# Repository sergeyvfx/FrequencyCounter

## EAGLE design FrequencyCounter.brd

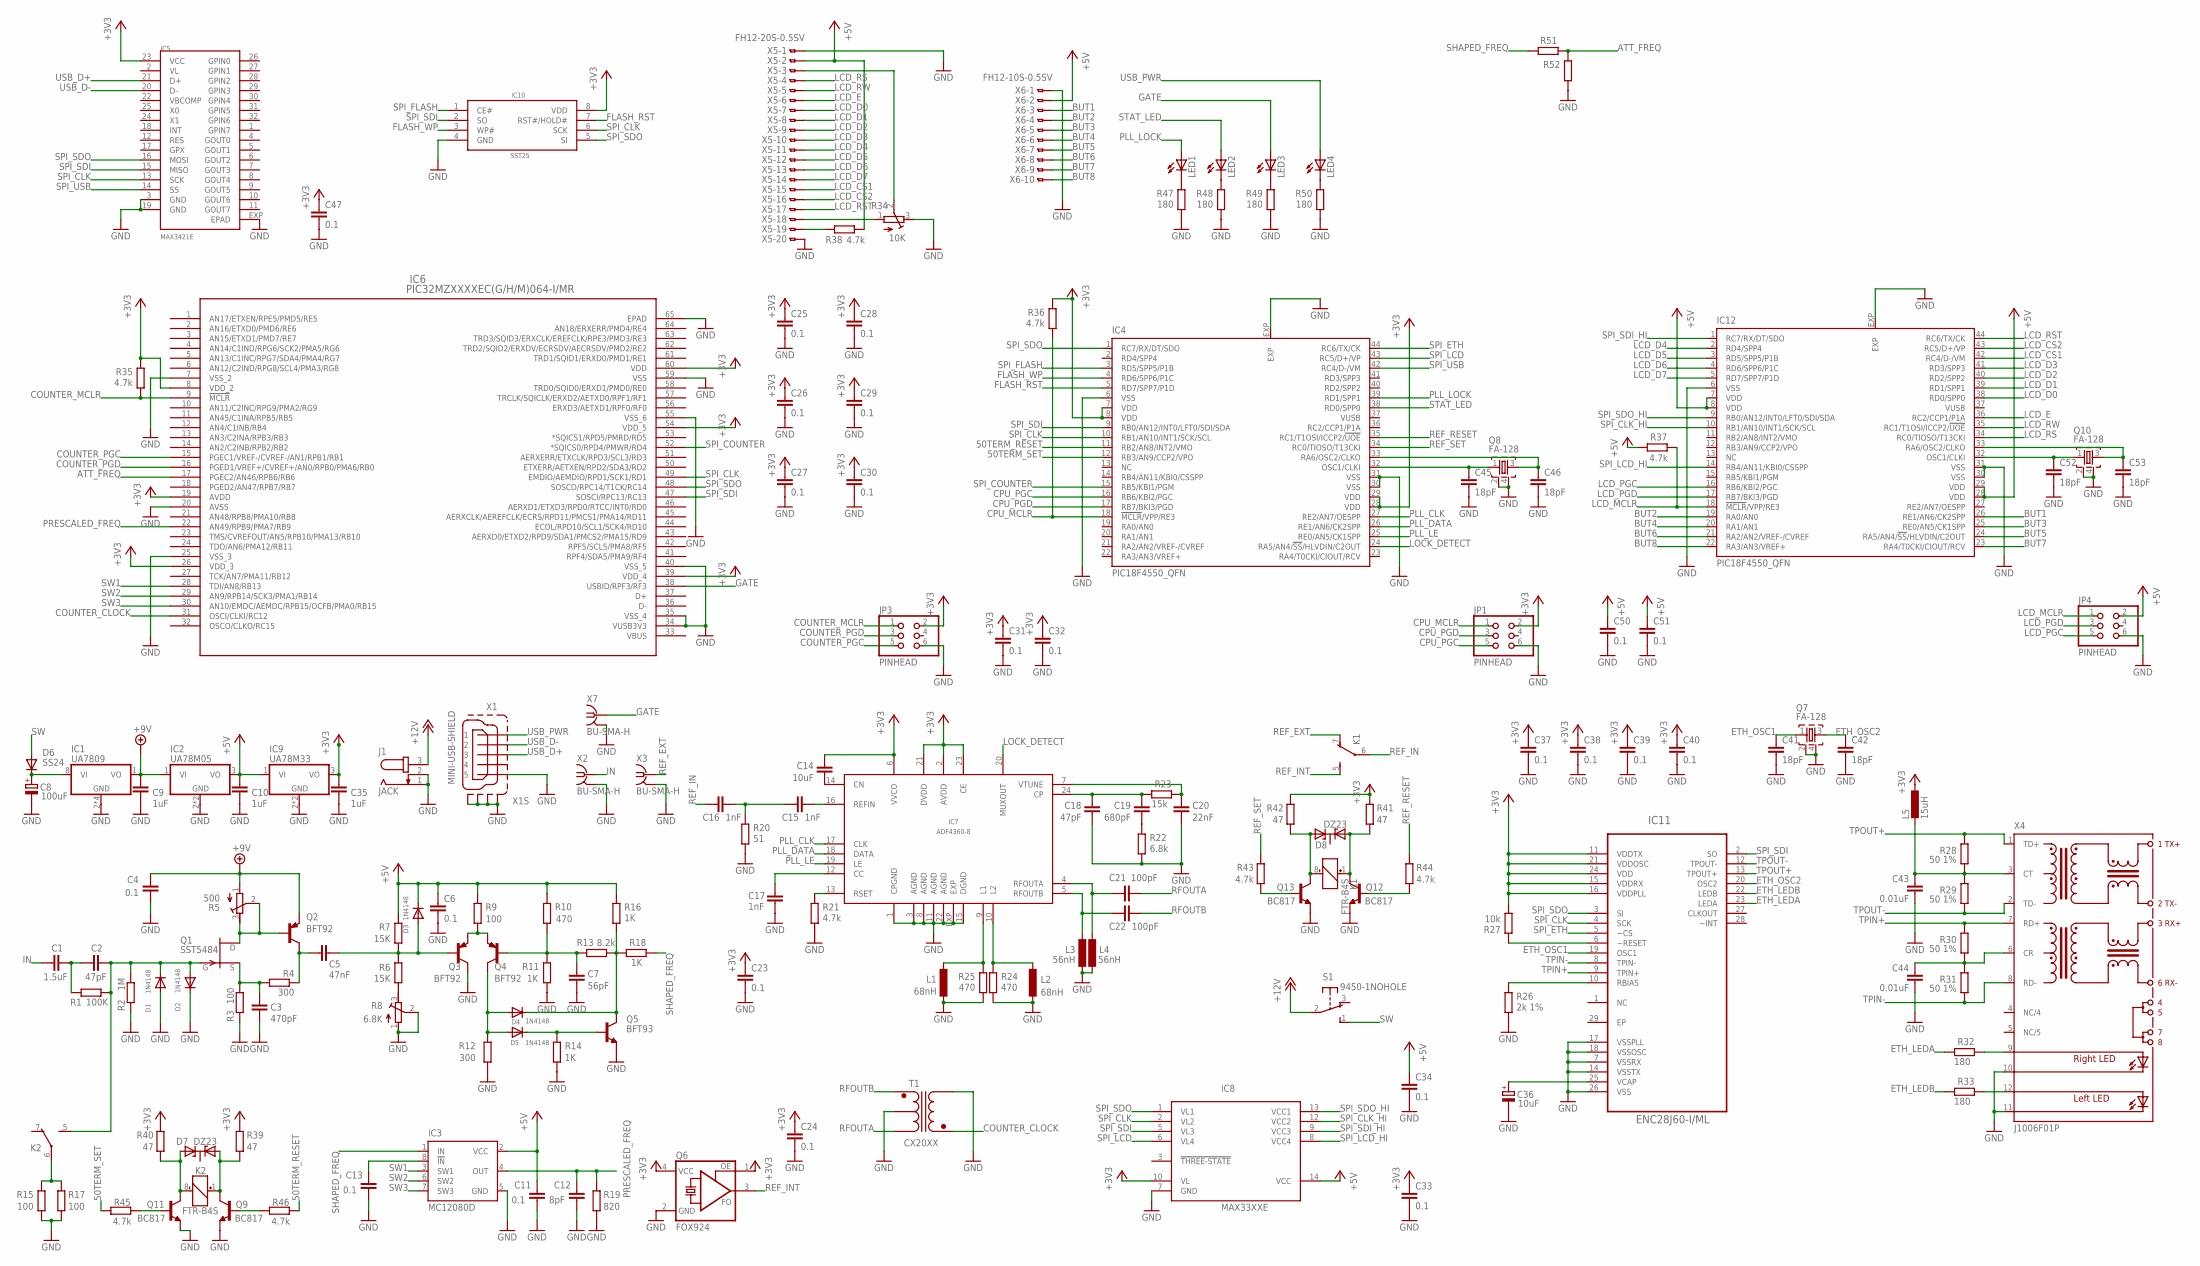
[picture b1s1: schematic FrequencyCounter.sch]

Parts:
C1: 1.5uF; C0603
C2, C18: 47pF; C0603
C3: 470pF; C0603
C4, C6, C11, C13, C23, C24, C25, C26, C27, C28, C29, C30, C31, C32, C33, C34, C37, C38, C39, C40, C47, C50, C51: 0.1; C0603
C5: 47nF; C0603
C7: 56pF; C0603
C8: 100uF; D/7343-31R
C9, C10, C35: 1uF; C0603
C12: 8pF; C0603
C14: 10uF; C0603
C15, C16, C17: 1nF; C0603
C19: 680pF; C0603
C20: 22nF; C0603
C21, C22: 100pF; C0603
C36: 10uF; B/3528-21R
C41, C42, C45, C46, C52, C53: 18pF; C0603
C43, C44: 0.01uF; C0603
D1, D2, D3, D4, D5: 1N4148; SOD-123
D6: SS24; DO214AA
D7, D8: DZ23; SOT23
IC1: UA7809; SOIC8
IC2: UA78M05; SOT223
IC3: MC12080D; SO08
IC4, IC12: PIC18F4550_QFN; QFN44ML8X8
IC5: MAX3421E; TQFN32
IC6: PIC32MZXXXXEC(G/H/M)064-I/MR; QFN64_9X9MC
IC7: ADF4360-8; LFCSP24
IC8: MAX33XXE; TSSOP14
IC9: UA78M33; SOT223
IC10: SST25; SOIC8
IC11: ENC28J60-I/ML; QFN65P600X600X100-29N
J1: JACK; SPC4077
JP1, JP3, JP4: PINHEAD; 2X03_1.27
K1, K2: FTR-B4S
L1, L2: 68nH; L2012C
L3, L4: 56nH; L2012C
L5: 15uH; L2012C
LED1, LED2, LED3, LED4: LEDCHIP-LED0805; CHIP-LED0805
Q1: SST5484; SOT23
Q2, Q3, Q4: BFT92; SOT23-BEC
Q5: BFT93; SOT23-BEC
Q6: FOX924
Q7, Q8, Q10: FA-128
Q9, Q11, Q12, Q13: BC817; SOT23-BEC
R1: 100K; R0603
R2: 1M; R0603
R3, R9, R15, R17: 100; R0603
R4, R12: 300; R0603
R5: 500; RTRIM4G/J
R6, R7: 15K; R0603
R8: 6.8K; RTRIM4G/J
R10, R24, R25: 470; R0603
R11, R14, R16, R18: 1K; R0603
R13: 8.2k; R0603
R19: 820; R0603
R20: 51; R0603
R21, R35, R36, R37, R38, R43, R44, R45, R46: 4.7k; R0603
R22: 6.8k; R0603
R23: 15k; R0603
R26: 2k 1%; R0603
R27: 10k; R0603
R28, R29, R30, R31: 50 1%; R0603
R32, R33, R47, R48, R49, R50: 180; R0603
R34: 10K; RTRIM4G/J
R39, R40, R41, R42: 47; R0603
R51, R52: R-EU_R0603; R0603
S1: 9450-1NOHOLE; 9450-1-NOHOLE
T1: CX20XX; PULSE_CX20
X1: MINI-USB-SHIELD; UX60A-MB-5ST
X2, X3, X7: BU-SMA-H
X4: J1006F01P; J1
X5: FH12-20S-0.5SV
X6: FH12-10S-0.5SV

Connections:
50TERM_RESET: IC4.11 (RB2/AN8/INT2/VMO), R46.2
50TERM_SET: IC4.12 (RB3/AN9/CCP2/VPO), R45.1
+3V3: C14.2, C23.1, C24.1, C25.1, C26.1, C27.1, C28.1, C29.1, C30.1, C31.1, C32.1, C33.1, C35.1, C37.1, C38.1, C39.1, C40.1, C47.1, IC4.7 (VDD), IC4.8 (VDD), IC4.28 (VDD), IC4.29 (VDD), IC5.23 (VCC), IC6.8 (VDD_2), IC6.19 (AVDD), IC6.26 (VDD_3), IC6.39 (VDD_4), IC6.54 (VDD_5), IC6.60 (VDD), IC7.2 (AVDD), IC7.6 (VVCO), IC7.21 (DVDD), IC7.23 (CE), IC8.10 (VL), IC9.3 (VO), IC10.8 (VDD), IC11.11 (VDDTX), IC11.15 (VDDRX), IC11.16 (VDDPLL), IC11.21 (VDDOSC), IC11.24 (VDD), JP1.2, JP3.2, L5.1, Q6.1 (OE), Q6.4 (VCC), R27.2, R35.1, R36.1, R39.1, R40.1, R41.1, R42.1
+5V: C6.1, C10.1, C11.1, C34.1, C50.1, C51.1, D3.C, IC2.3 (VO), IC3.2 (VCC), IC8.14 (VCC), IC9.1 (VI), IC12.7 (VDD), IC12.8 (VDD), IC12.28 (VDD), IC12.29 (VDD), JP4.2, R7.1, R9.1, R10.1, R16.1, R37.1, R38.2, X5.2, X6.2
+9V: C4.1, C9.1, IC1.1 (VO), IC2.1 (VI), Q2.E, R5.1 (A)
+12V: J1.3, S1.2
ATT_FREQ: IC6.17 (PGEC2/AN46/RPB6/RB6), R51.2, R52.1
BUT1: IC12.26 (RE1/AN6/CK2SPP), X6.3
BUT2: IC12.19 (RA0/AN0), X6.4
BUT3: IC12.25 (RE0/AN5/CK1SPP), X6.5
BUT4: IC12.20 (RA1/AN1), X6.6
BUT5: IC12.24 (RA5/AN4/!SS!/HLVDIN/C2OUT), X6.7
BUT6: IC12.21 (RA2/AN2/VREF-/CVREF), X6.8
BUT7: IC12.23 (RA4/T0CKI/CIOUT/RCV), X6.9
BUT8: IC12.22 (RA3/AN3/VREF+), X6.10
COUNTER_CLOCK: IC6.31 (OSCI/CLKI/RC12), T1.P$4
COUNTER_MCLR: IC6.9 (!MCLR!), JP3.1, R35.2
COUNTER_PGC: IC6.15 (PGEC1/VREF-/CVREF-/AN1/RPB1/RB1), JP3.5
COUNTER_PGD: IC6.16 (PGED1/VREF+/CVREF+/AN0/RPB0/PMA6/RB0), JP3.3
CPU_MCLR: IC4.18 (!MCLR!/VPP/RE3), JP1.1, R36.2
CPU_PGC: IC4.16 (RB6/KBI2/PGC), JP1.5
CPU_PGD: IC4.17 (RB7/BKI3/PGD), JP1.3
ETH_LEDA: IC11.23 (LEDA), R32.2
ETH_LEDB: IC11.22 (LEDB), R33.2
ETH_OSC1: C41.1, IC11.19 (OSC1), Q7.1
ETH_OSC2: C42.1, IC11.20 (OSC2), Q7.3
FLASH_RST: IC4.5 (RD7/SPP7/P1D), IC10.7 (RST#/HOLD#)
FLASH_WP: IC4.4 (RD6/SPP6/P1C), IC10.3 (WP#)
GATE: IC6.38 (USBID/RPF3/RF3), LED3.A, X7.1
GND: C3.2, C4.2, C6.2, C7.1, C8.-, C9.2, C10.2, C11.2, C12.2, C13.2, C17.2, C18.1, C20.1, C23.2, C24.2, C25.2, C26.2, C27.2, C28.2, C29.2, C30.2, C31.2, C32.2, C33.2, C34.2, C35.2, C36.-, C37.2, C38.2, C39.2, C40.2, C41.2, C42.2, C43.2, C44.2, C45.2, C46.2, C47.2, C50.2, C51.2, C52.2, C53.2, D1.A, D2.C, IC1.2 (GND), IC1.3 (GND), IC1.6 (GND), IC1.7 (GND), IC2.2 (GND), IC2.4 (GND), IC3.5 (GND), IC4.6 (VSS), IC4.30 (VSS), IC4.31 (VSS), IC4.EXP, IC5.3 (GND), IC5.19 (GND), IC5.EXP (EPAD), IC6.7 (VSS_2), IC6.20 (AVSS), IC6.25 (VSS_3), IC6.34 (VUSB3V3), IC6.35 (VSS_4), IC6.40 (VSS_5), IC6.55 (VSS_6), IC6.59 (VSS), IC6.65 (EPAD), IC7.1 (CPGND), IC7.3 (AGND), IC7.8 (AGND), IC7.11 (AGND), IC7.15 (DGND), IC7.22 (AGND), IC7.EXP, IC8.7 (GND), IC9.2 (GND), IC9.4 (GND), IC10.4 (GND), IC11.7 (VSSRX), IC11.14 (VSSTX), IC11.17 (VSSPLL), IC11.18 (VSSOSC), IC11.26 (VSS), IC12.6 (VSS), IC12.30 (VSS), IC12.31 (VSS), IC12.EXP, J1.1, J1.2, JP1.6, JP3.6, JP4.6, L1.2, L2.2, L3.2, L4.2, Q3.C, Q5.E, Q6.2 (GND), Q7.2, Q7.4, Q8.2, Q8.4, Q9.E, Q10.2, Q10.4, Q11.E, Q12.E, Q13.E, R2.2, R3.2, R8.1 (A), R8.2 (S), R11.2, R12.2, R14.2, R15.2, R17.2, R19.2, R20.2, R21.2, R22.2, R24.2, R25.2, R26.2, R34.3 (E), R47.2, R48.2, R49.2, R50.2, R52.2, T1.P$2, T1.P$6, X1.5, X1.M1 (S1), X1.M2 (S2), X1.M3 (S3), X1.M4 (S4), X2.2, X2.3 (2), X2.4 (2), X2.5 (2), X3.2, X3.3 (2), X3.4 (2), X3.5 (2), X4.10 (C-R), X4.11 (C-L), X5.1, X5.20, X6.1, X7.2, X7.3 (2), X7.4 (2), X7.5 (2)
IN: C1.1, X2.1
LCD_CS1: IC12.42 (RC4/D-/VM), X5.15
LCD_CS2: IC12.43 (RC5/D+/VP), X5.16
LCD_D0: IC12.38 (RD0/SPP0), X5.7
LCD_D1: IC12.39 (RD1/SPP1), X5.8
LCD_D2: IC12.40 (RD2/SPP2), X5.9
LCD_D3: IC12.41 (RD3/SPP3), X5.10
LCD_D4: IC12.2 (RD4/SPP4), X5.11
LCD_D5: IC12.3 (RD5/SPP5/P1B), X5.12
LCD_D6: IC12.4 (RD6/SPP6/P1C), X5.13
LCD_D7: IC12.5 (RD7/SPP7/P1D), X5.14
LCD_E: IC12.36 (RC2/CCP1/P1A), X5.6
LCD_MCLR: IC12.18 (!MCLR!/VPP/RE3), JP4.1, R37.2
LCD_PGC: IC12.16 (RB6/KBI2/PGC), JP4.5
LCD_PGD: IC12.17 (RB7/BKI3/PGD), JP4.3
LCD_RS: IC12.34 (RC0/TIOSO/T13CKI), X5.4
LCD_RST: IC12.44 (RC6/TX/CK), X5.17
LCD_RW: IC12.35 (RC1/T1OSI/ICCP2/!UOE), X5.5
LOCK_DETECT: IC4.24 (RA5/AN4/!SS!/HLVDIN/C2OUT), IC7.20 (MUXOUT)
unnamed: C2.2, D1.C, D2.A, K2.5 (S), Q1.3 (G), R1.1, R2.1
unnamed: C1.2, C2.1, R1.2
unnamed: C3.1, Q1.2 (S), R3.1, R4.2
unnamed: Q1.1 (D), Q2.B, R5.2 (S), R5.3 (E)
unnamed: C5.2, Q2.C, R4.1
unnamed: R6.2, R8.3 (E)
unnamed: C5.1, D3.A, Q3.B, R6.1, R7.2
unnamed: Q3.E, Q4.E, R9.2
unnamed: C7.2, Q4.B, R10.2, R11.1, R13.2
unnamed: D4.A, D5.A, Q4.C, R12.1
unnamed: D4.C, Q5.C, R13.1, R16.2, R18.2
unnamed: D5.C, Q5.B, R14.1
unnamed: C8.+, D6.C, IC1.8 (VI)
unnamed: K2.6, R15.1, R17.1
unnamed: C14.1, IC7.14 (CN)
unnamed: C13.1, IC3.8 (!IN)
unnamed: C15.1, IC7.16 (REFIN)
unnamed: C15.2, C16.1, R20.1
unnamed: C17.1, IC7.12 (CC)
unnamed: IC7.13 (RSET), R21.1
unnamed: C19.1, R22.1
unnamed: C21.1, IC7.4 (RFOUTA), L4.1
unnamed: C20.2, IC7.7 (VTUNE), R23.1
unnamed: C18.2, C19.2, IC7.24 (CP), R23.2
unnamed: C22.2, IC7.5 (RFOUTB), L3.1
unnamed: IC7.10 (L2), L2.1, R24.1
unnamed: IC7.9 (L1), L1.1, R25.1
unnamed: C53.1, IC12.33 (RA6/OSC2/CLKO), Q10.3
unnamed: C46.1, IC4.33 (RA6/OSC2/CLKO), Q8.3
unnamed: C45.1, IC4.32 (OSC1/CLKI), Q8.1
unnamed: C36.+, IC11.25 (VCAP)
unnamed: IC11.10 (RBIAS), R26.1
unnamed: C43.1, L5.2, R28.1, R29.2, X4.3 (CT)
unnamed: IC11.6 (~RESET), R27.1
unnamed: R32.1, X4.9 (A-R)
unnamed: R33.1, X4.12 (A-L)
unnamed: C44.1, R30.1, R31.2, X4.6 (CR)
unnamed: C52.1, IC12.32 (OSC1/CLKI), Q10.1
unnamed: R34.2 (S), X5.3
unnamed: R34.1 (A), X5.18
unnamed: R38.1, X5.19
unnamed: D7.2 (A2), K2.8 (-), Q11.C, R40.2
unnamed: D8.2 (A2), K1.8 (-), Q13.C, R42.2
unnamed: D7.1 (A1), K2.1 (+), Q9.C, R39.2
unnamed: D8.1 (A1), K1.1 (+), Q12.C, R41.2
unnamed: Q13.B, R43.2
unnamed: Q12.B, R44.2
unnamed: Q11.B, R45.2
unnamed: Q9.B, R46.1
unnamed: LED1.C, R47.1
unnamed: LED2.C, R48.1
unnamed: LED3.C, R49.1
unnamed: LED4.C, R50.1
PLL_CLK: IC4.27 (RE2/AN7/OESPP), IC7.17 (CLK)
PLL_DATA: IC4.26 (RE1/AN6/CK2SPP), IC7.18 (DATA)
PLL_LE: IC4.25 (RE0/AN5/CK1SPP), IC7.19 (LE)
PLL_LOCK: IC4.39 (RD1/SPP1), LED1.A
PRESCALED_FREQ: C12.1, IC3.4 (OUT), IC6.22 (AN49/RPB9/PMA7/RB9), R19.1
REF_EXT: K1.7 (O), X3.1
REF_IN: C16.2, K1.6
REF_INT: K1.5 (S), Q6.3 (FO)
REF_RESET: IC4.35 (RC1/T1OSI/ICCP2/!UOE), R44.1
REF_SET: IC4.34 (RC0/TIOSO/T13CKI), R43.1
RFOUTA: C21.2, T1.P$3
RFOUTB: C22.1, T1.P$1
SHAPED_FREQ: IC3.1 (IN), R18.1, R51.1
SPI_CLK: IC4.10 (RB1/AN10/INT1/SCK/SCL), IC5.13 (SCK), IC6.49 (EMDIO/AEMDIO/RPD1/SCK1/RD1), IC8.2 (VL2), IC10.6 (SCK), IC11.4 (SCK)
SPI_CLK_HI: IC8.12 (VCC2), IC12.10 (RB1/AN10/INT1/SCK/SCL)
SPI_COUNTER: IC4.15 (RB5/KBI1/PGM), IC6.52 (*SQICS0/RPD4/PMWR/RD4)
SPI_ETH: IC4.44 (RC6/TX/CK), IC11.5 (~CS)
SPI_FLASH: IC4.3 (RD5/SPP5/P1B), IC10.1 (CE#)
SPI_LCD: IC4.43 (RC5/D+/VP), IC8.6 (VL4)
SPI_LCD_HI: IC8.8 (VCC4), IC12.14 (RB4/AN11/KBI0/CSSPP)
SPI_SDI: IC4.9 (RB0/AN12/INT0/LFT0/SDI/SDA), IC5.15 (MISO), IC6.47 (SOSCI/RPC13/RC13), IC8.5 (VL3), IC10.2 (SO), IC11.2 (SO)
SPI_SDI_HI: IC8.9 (VCC3), IC12.1 (RC7/RX/DT/SDO)
SPI_SDO: IC4.1 (RC7/RX/DT/SDO), IC5.16 (MOSI), IC6.48 (SOSCO/RPC14/T1CK/RC14), IC8.1 (VL1), IC10.5 (SI), IC11.3 (SI)
SPI_SDO_HI: IC8.13 (VCC1), IC12.9 (RB0/AN12/INT0/LFT0/SDI/SDA)
SPI_USB: IC4.42 (RC4/D-/VM), IC5.14 (SS)
STAT_LED: IC4.38 (RD0/SPP0), LED2.A
SW: D6.A, S1.1 (S)
SW1: IC3.3 (SW1), IC6.28 (TDI/AN8/RB13)
SW2: IC3.6 (SW2), IC6.29 (AN9/RPB14/SCK3/PMA1/RB14)
SW3: IC3.7 (SW3), IC6.30 (AN10/EMDC/AEMDC/RPB15/OCFB/PMA0/RB15)
TPIN+: IC11.9 (TPIN+), R30.2, X4.7 (RD+)
TPIN-: IC11.8 (TPIN-), R31.1, X4.8 (RD-)
TPOUT+: IC11.13 (TPOUT+), R28.2, X4.1 (TD+)
TPOUT-: IC11.12 (TPOUT-), R29.1, X4.2 (TD-)
USB_D+: IC5.21 (D+), X1.3
USB_D-: IC5.20 (D-), X1.2
USB_PWR: LED4.A, X1.1
VBUS: IC6.33 (VBUS)

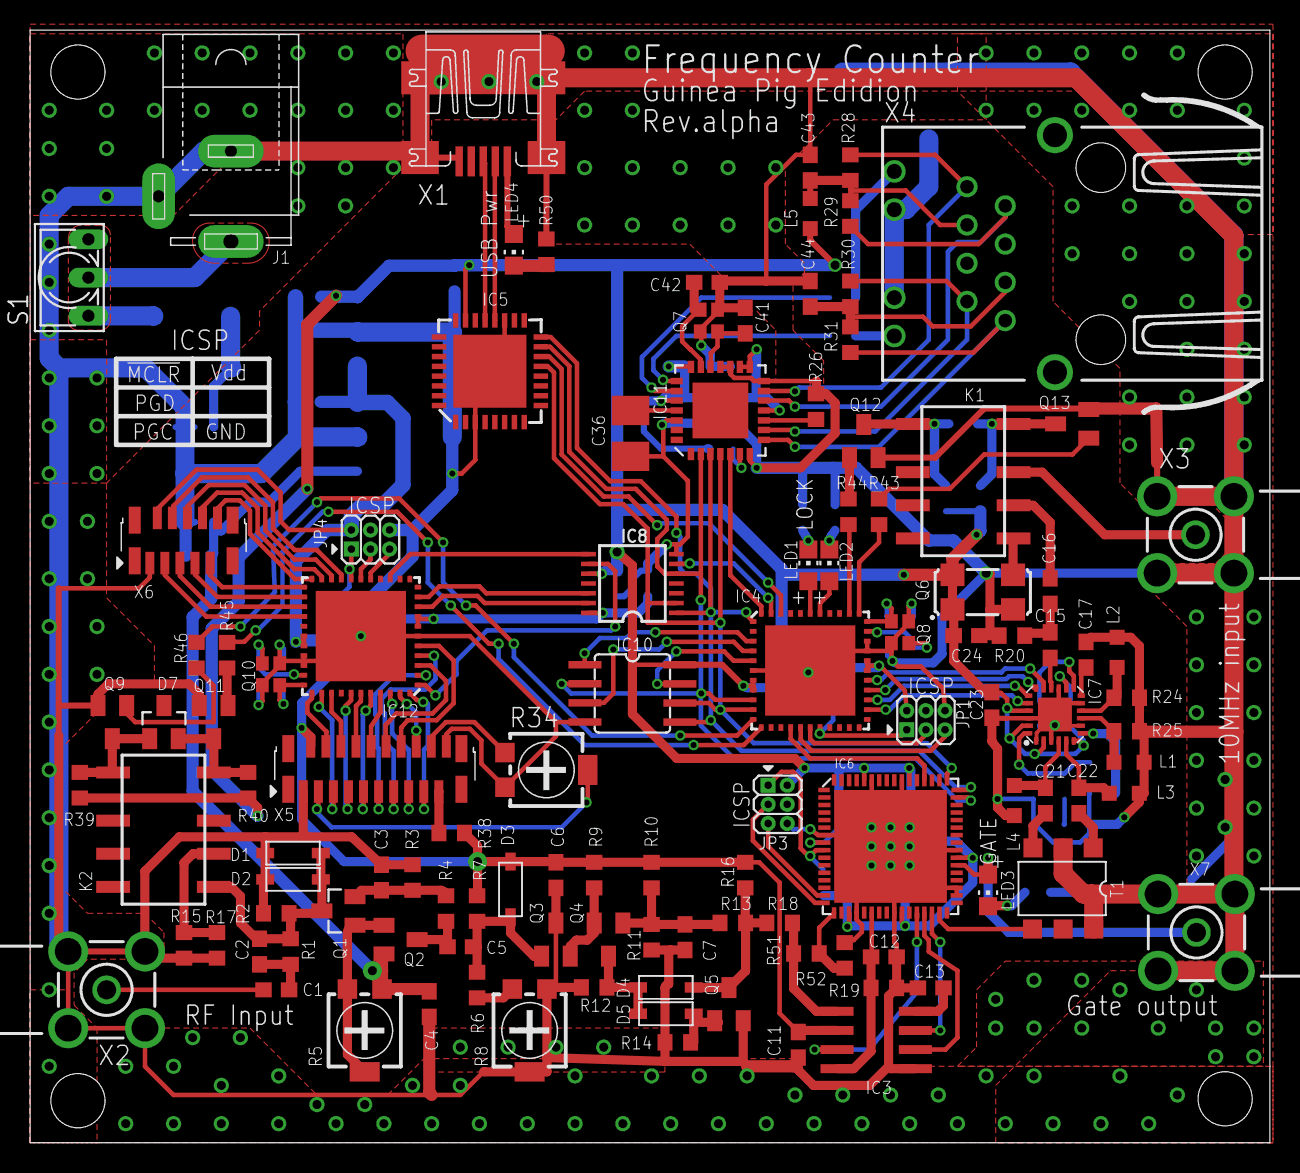
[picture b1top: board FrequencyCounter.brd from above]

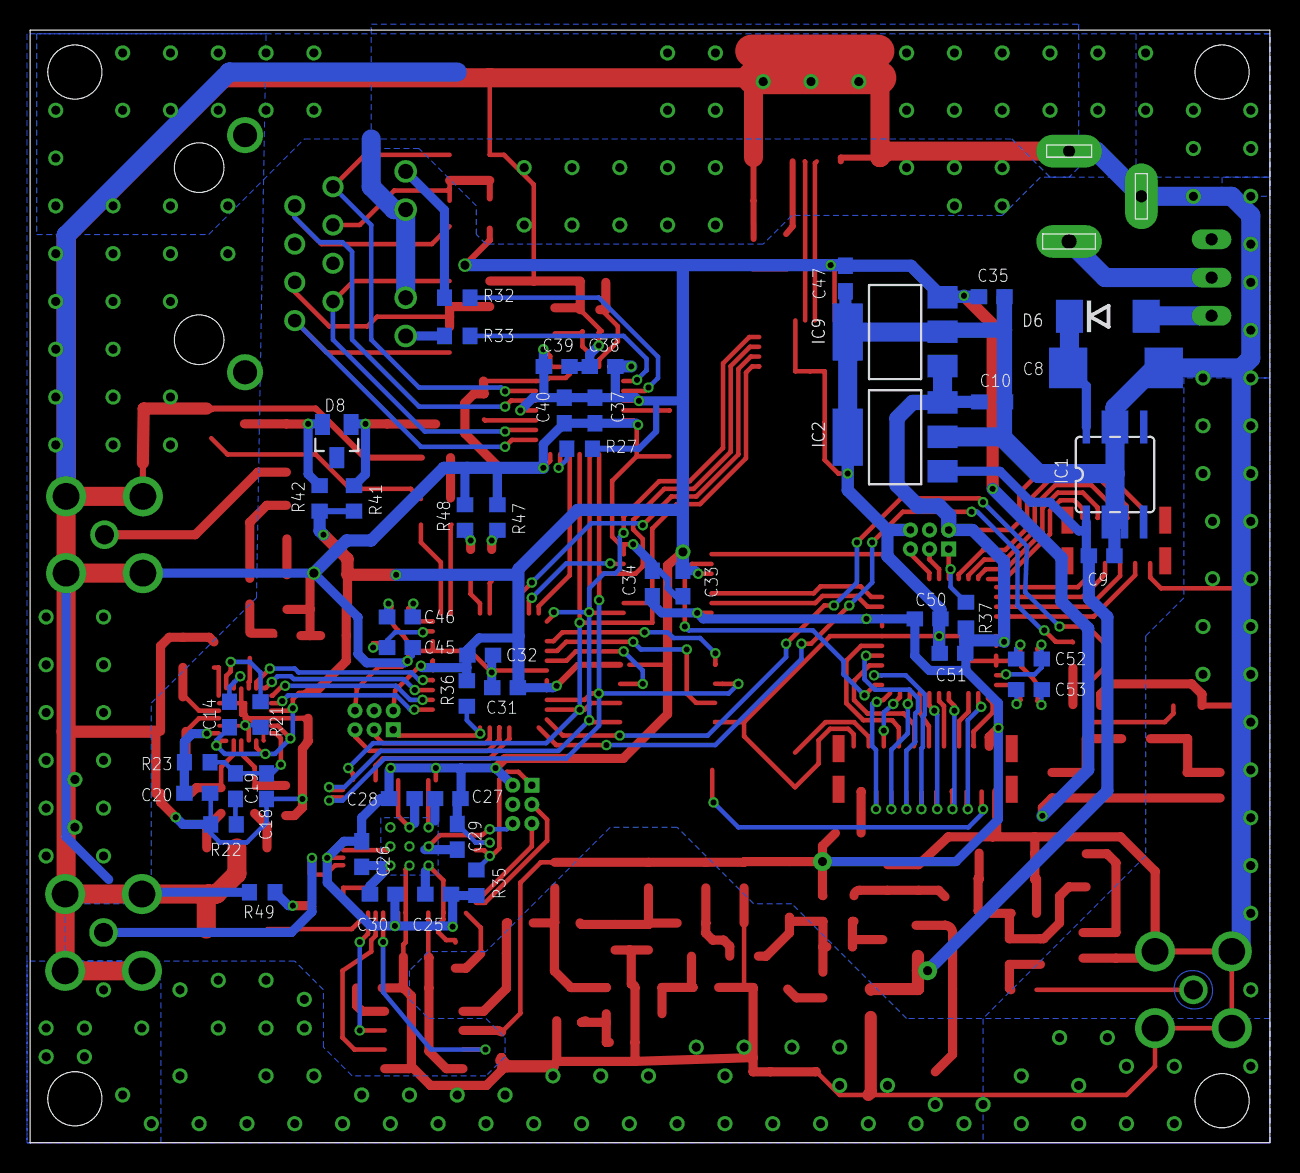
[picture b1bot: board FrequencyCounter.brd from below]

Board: 2 copper layers, 82.3 x 73.9 mm, 160 parts (48 on the bottom side), 139 nets.

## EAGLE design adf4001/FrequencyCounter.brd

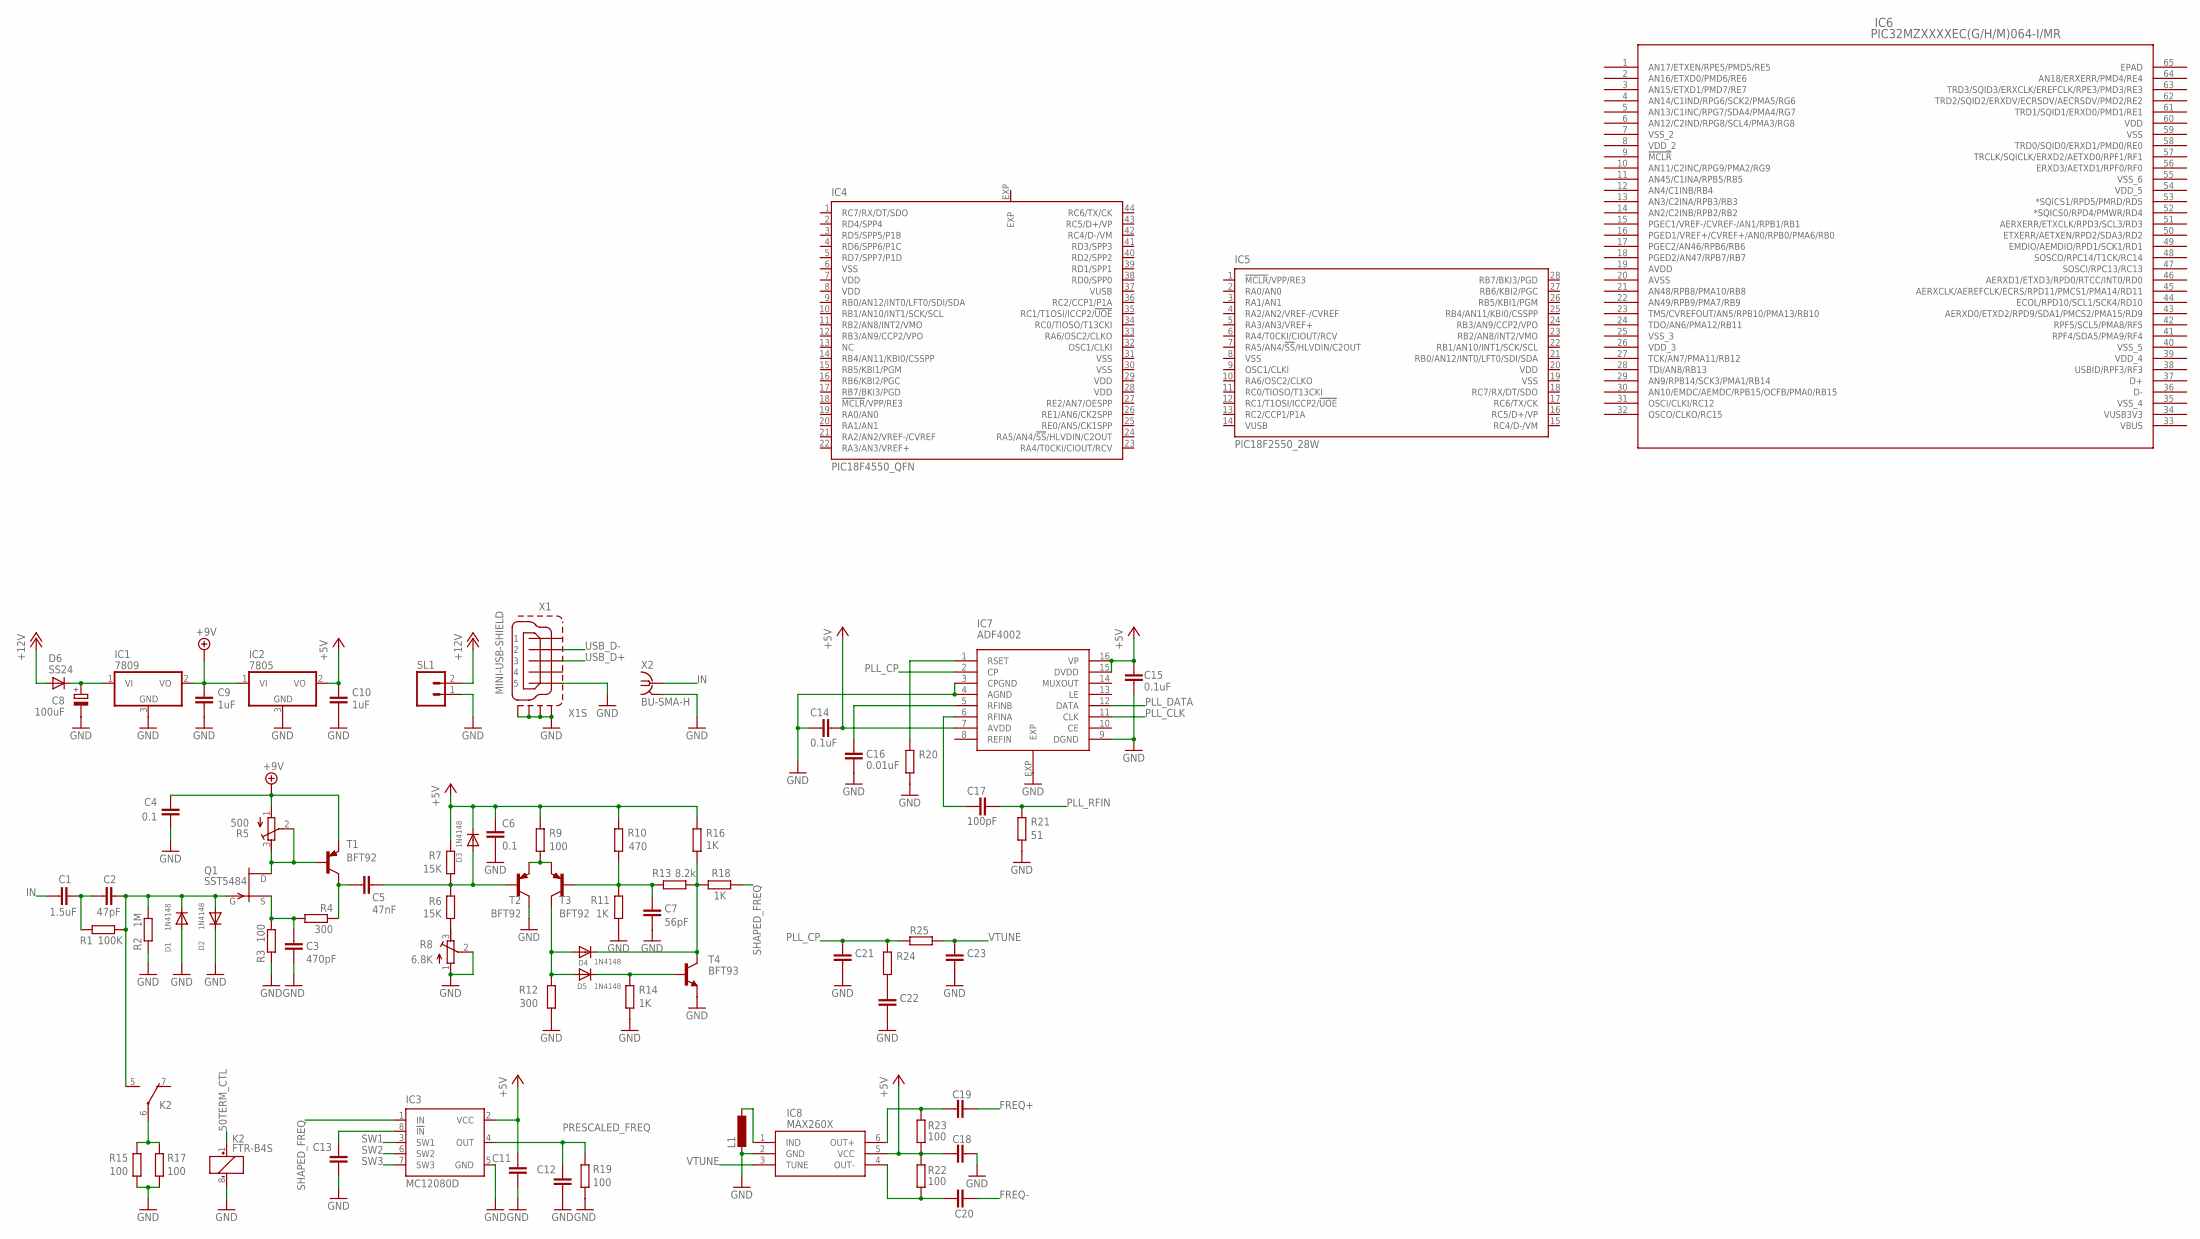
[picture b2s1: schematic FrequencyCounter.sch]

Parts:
C1: 1.5uF; C0805
C2: 47pF; C0805
C3: 470pF; C0805
C4, C6: 0.1; C0805
C5: 47nF; C0805
C7: 56pF; C0805
C8: 100uF; D/7343-31R
C9, C10: 1uF; C0805
C11, C12, C13, C18, C19, C20, C21, C22, C23: C-EUC0805; C0805
C14, C15: 0.1uF; C0805
C16: 0.01uF; C0805
C17: 100pF; C0805
D1, D2, D3, D4, D5: 1N4148; SOD-123
D6: SS24; DO214AA
IC1: 7809; TO252
IC2: 7805; TO252
IC3: MC12080D; SO08
IC4: PIC18F4550_QFN; QFN44ML8X8
IC5: PIC18F2550_28W; SO28W
IC6: PIC32MZXXXXEC(G/H/M)064-I/MR; QFN64_9X9MC
IC7: ADF4002; LFCSP16
IC8: MAX260X; SOT-23-6
K2: FTR-B4S
L1: L-EUL3225P; L3225P
Q1: SST5484; SOT23
R1: 100K; R0805
R2: 1M; R0805
R3, R9, R15, R17, R19, R22, R23: 100; R0805
R4, R12: 300; R0805
R5: 500; RTRIM4G/J
R6, R7: 15K; R0805
R8: 6.8K; RTRIM4G/J
R10: 470; R0805
R11, R14, R16, R18: 1K; R0805
R13: 8.2k; R0805
R20, R24, R25: R-EU_R0805; R0805
R21: 51; R0805
SL1: M02; 02P
T1, T2, T3: BFT92; SOT23-BEC
T4: BFT93; SOT23-BEC
X1: MINI-USB-SHIELD; UX60A-MB-5ST
X2: BU-SMA-H

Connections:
50TERM_CTL: K2.1 (+)
+5V: C6.1, C10.1, C11.1, C14.1, C15.2, C18.1, D3.C, IC2.2 (VO), IC3.2 (VCC), IC7.7 (AVDD), IC7.15 (DVDD), IC7.16 (VP), IC8.5 (VCC), R7.1, R9.1, R10.1, R16.1, R22.2, R23.1
+9V: C4.1, C9.1, IC1.2 (VO), IC2.1 (VI), R5.1 (A), T1.E
+12V: D6.A, SL1.2
AVDD: IC6.19 (AVDD)
AVSS: IC6.20 (AVSS)
FREQ+: C19.2
FREQ-: C20.2
GND: C3.2, C4.2, C6.2, C7.1, C8.-, C9.2, C10.2, C11.2, C12.2, C13.2, C14.2, C15.1, C16.2, C18.2, C21.1, C22.1, C23.1, D1.A, D2.C, IC1.3 (GND), IC2.3 (GND), IC3.5 (GND), IC7.3 (CPGND), IC7.4 (AGND), IC7.9 (DGND), IC7.EXP, IC8.2 (GND), K2.8 (-), L1.2, R2.2, R3.2, R8.1 (A), R8.2 (S), R11.2, R12.2, R14.2, R15.2, R17.2, R19.2, R20.2, R21.2, SL1.1, T2.C, T4.E, X1.5, X1.M1 (S1), X1.M2 (S2), X1.M3 (S3), X1.M4 (S4), X2.2, X2.3 (2), X2.4 (2), X2.5 (2)
IN: C1.1, X2.1
unnamed: C2.2, D1.C, D2.A, K2.5 (S), Q1.3 (G), R1.1, R2.1
unnamed: C1.2, C2.1, R1.2
unnamed: C3.1, Q1.2 (S), R3.1, R4.2
unnamed: Q1.1 (D), R5.2 (S), R5.3 (E), T1.B
unnamed: C5.2, R4.1, T1.C
unnamed: R6.2, R8.3 (E)
unnamed: C5.1, D3.A, R6.1, R7.2, T2.B
unnamed: R9.2, T2.E, T3.E
unnamed: C7.2, R10.2, R11.1, R13.2, T3.B
unnamed: D4.A, D5.A, R12.1, T3.C
unnamed: D4.C, R13.1, R16.2, R18.2, T4.C
unnamed: D5.C, R14.1, T4.B
unnamed: C8.+, D6.C, IC1.1 (VI)
unnamed: K2.6, R15.1, R17.1
unnamed: C16.1, IC7.5 (RFINB)
unnamed: C13.1, IC3.8 (!IN)
unnamed: IC7.1 (RSET), R20.1
unnamed: C17.2, IC7.6 (RFINA)
unnamed: IC8.1 (IND), L1.1
unnamed: C20.1, IC8.4 (OUT-), R22.1
unnamed: C19.1, IC8.6 (OUT+), R23.2
unnamed: C22.2, R24.2
PLL_CLK: IC7.11 (CLK)
PLL_CP: C21.2, IC7.2 (CP), R24.1, R25.1
PLL_DATA: IC7.12 (DATA)
PLL_RFIN: C17.1, R21.1
PRESCALED_FREQ: C12.1, IC3.4 (OUT), R19.1
SHAPED_FREQ: IC3.1 (IN), R18.1
SW1: IC3.3 (SW1)
SW2: IC3.6 (SW2)
SW3: IC3.7 (SW3)
USB_D+: X1.3
USB_D-: X1.2
VBUS: IC6.33 (VBUS)
VDD: IC4.7 (VDD), IC4.8 (VDD), IC4.28 (VDD), IC4.29 (VDD), IC5.20 (VDD), IC6.60 (VDD)
VDD_2: IC6.8 (VDD_2)
VDD_3: IC6.26 (VDD_3)
VDD_4: IC6.39 (VDD_4)
VDD_5: IC6.54 (VDD_5)
VSS: IC4.6 (VSS), IC4.30 (VSS), IC4.31 (VSS), IC5.8 (VSS), IC5.19 (VSS), IC6.59 (VSS)
VSS_2: IC6.7 (VSS_2)
VSS_3: IC6.25 (VSS_3)
VSS_4: IC6.35 (VSS_4)
VSS_5: IC6.40 (VSS_5)
VSS_6: IC6.55 (VSS_6)
VTUNE: C23.2, IC8.3 (TUNE), R25.2
VUSB3V3: IC6.34 (VUSB3V3)

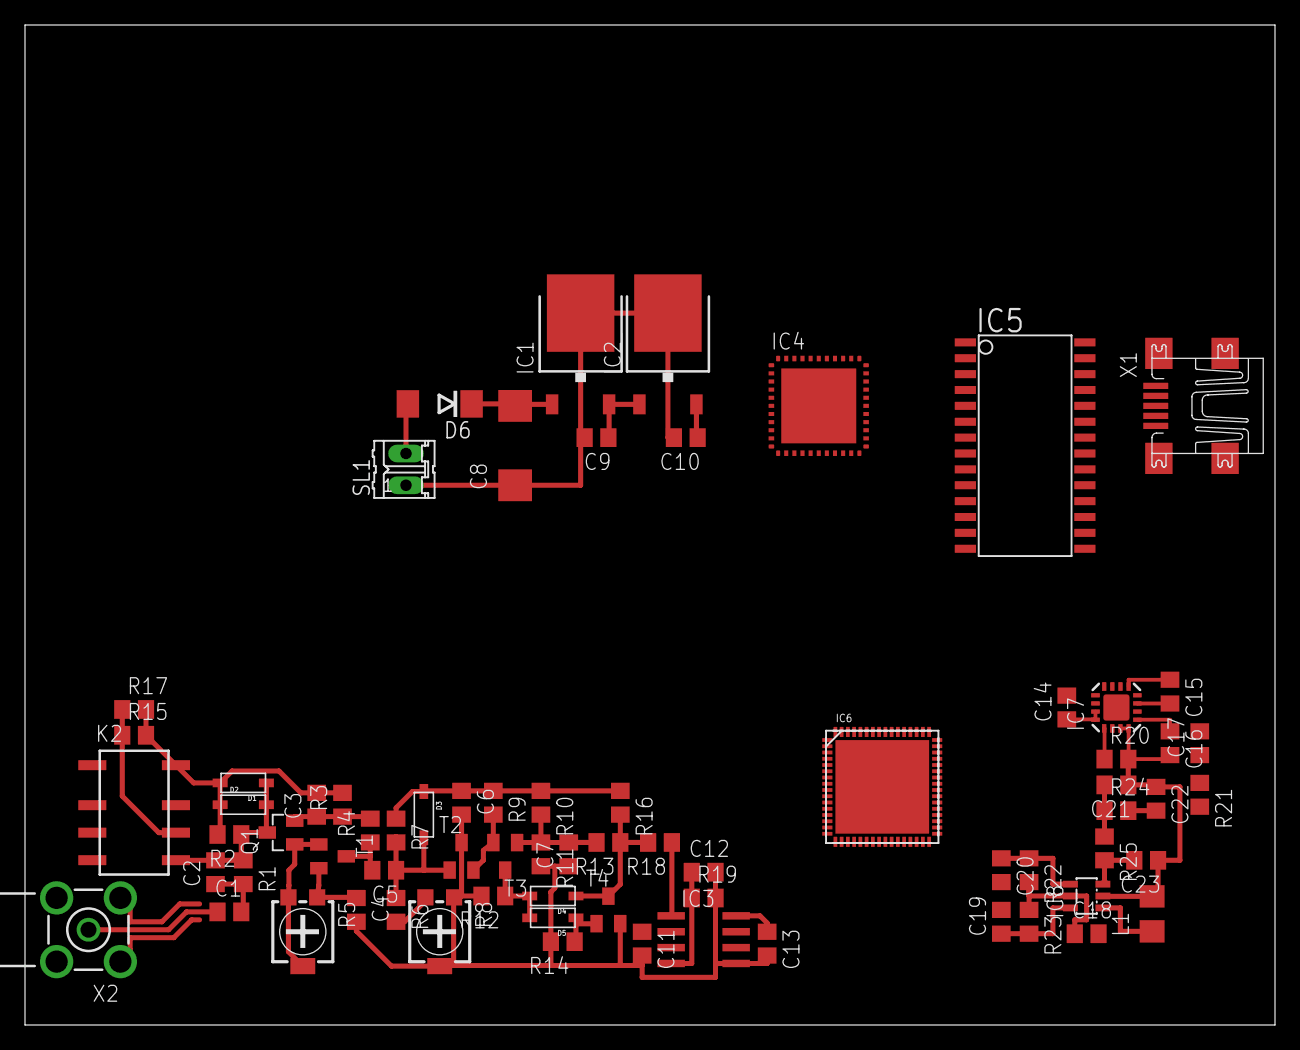
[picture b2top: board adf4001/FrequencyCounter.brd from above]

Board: 2 copper layers, 100.0 x 80.0 mm, 72 parts (0 on the bottom side), 34 nets.

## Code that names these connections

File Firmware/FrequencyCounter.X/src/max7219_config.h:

#ifndef MAX7219_CONFIG_H_
#define	MAX7219_CONFIG_H_

/* NOTE: ports shall be configured for the outout by the main function.
 *       Driver's code doesnt' touch TRIS bits at all.
 */

/* Port used to send data to driver's Din line. */
#define DOUT PORTAbits.RA2

/* Port used for driver's CLK line. */
#define CLK  PORTAbits.RA3

/* Port used for driver's LOAD line. */
#define LOAD PORTAbits.RA1
//#define LOAD PORTAbits.RA4

#endif	/* MAX7219_CONFIG_H_ */
